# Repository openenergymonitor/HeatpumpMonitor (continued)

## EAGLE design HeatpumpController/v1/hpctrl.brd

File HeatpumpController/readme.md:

# Heatpump Controller v1

An initial board design for a heat pump controller, designed for use with a Mitsubishi EcoDan with a FTC2b controller.

This board sits on top of a RaspberryPi and the very basic at this stage python scripting that runs on it can be found here: https://github.com/TrystanLea/heatpump_control

**Features:**

- 6x solid state relay outputs either PVT312, PVT412 or LH1546. Most of these are used to switch the volts free inputs on the FTC2b, e.g heating on, DHW mode etc.
- The PVT412 can drive up to 120mA AC which is 27.6W, can directly control a couple of AC low power solenoids/valves.
- 4x DS18B20 temperature sensor connections for cylinder and outside temperature sensors
- 0-5V voltage output to set EcoDan flow temperature
- A connection for the MBUS reader module here [USB_to_MBUS](https://github.com/openenergymonitor/HeatpumpMonitor/tree/master/Hardware/USB_to_MBUS) to read from heat meters. Later version could integrate this on the board.
- The Pi can connect via an modbus reader to a SDM120 single phase electricity meter, see [OEM Guide](https://guide.openenergymonitor.org/integrations/emonhub-interfacers/#reading-from-a-sdm120-single-phase-meter)

## Alternative approach (better?)

It looks like it is possible to issue commands directly via the CN105 connector on most Mitsubushi EcoDan controllers, which looks like a better and much cheaper approach than the above. Will be trying this myself soon:

- https://github.com/SwiCago/HeatPump
- https://www.geekzone.co.nz/forums.asp?forumid=73&topicid=265469
- https://web.archive.org/web/20171007190023/https://nicegear.co.nz/blog/hacking-a-mitsubishi-heat-pump-air-conditioner/
- https://gitter.im/Mitsubishi-CN105-Protocol-Decode/community
- https://github.com/m000c400/Mitsubishi-CN105-Protocol-Decode
- https://github.com/BartGijsbers/CN105Gateway
- https://www.zakon.org/robert/projects/MiniSplitPi/

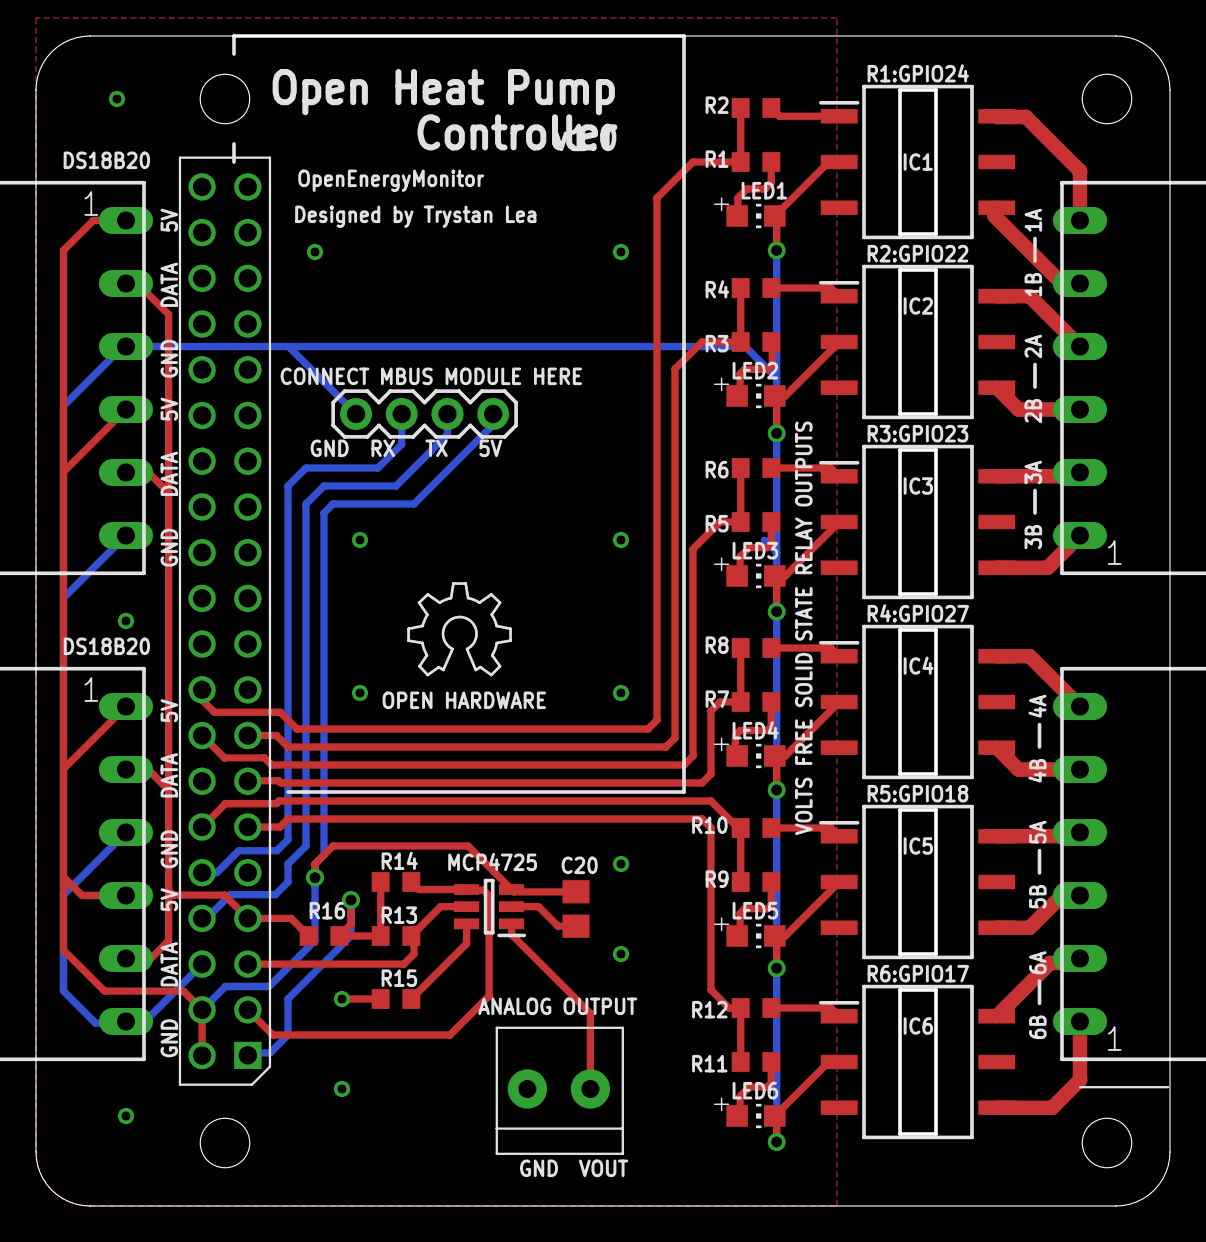
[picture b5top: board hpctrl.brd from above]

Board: 2 copper layers, 63.0 x 65.0 mm, 38 parts (0 on the bottom side), 40 nets.

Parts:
C20: 1uF; C0805
IC1, IC2, IC3, IC4, IC5, IC6: PVT312LSPBF; SOP254P978X342-6N
IC7: MCP4725A0T-E_CH; SOT95P270X145-6N
J1: 1X2-3.5MM
LED1, LED2, LED3, LED4, LED5, LED6: Red 1.85V; CHIP-LED0805
LOGO2: OSHW_LOGO_6MILX0200-NT; OSHW_6X200_NOTEXT
MBUS_SERIAL: 1X4-BIG; 1X04-BIG
PCB1: RPI3RPI3; RPI3
R1, R3, R4, R5, R6, R7, R8, R9, R10, R11, R12: 1K; R0603
R2: 1k; R0603
R13, R14, R15: 10k; R0603
R16: 4.7k; R0603
TB1, TB2, TB3, TB4: 3.5MM_TB_X6; 3.5MM_X6

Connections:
3V3: PCB1.P$1, R13.2, R14.2, R16.2
5V: C20.1, IC7.3, MBUS_SERIAL.1, PCB1.P$2, PCB1.P$4, TB3.P$1, TB3.P$4, TB4.P$1, TB4.P$4
DS18B20: PCB1.P$7, R16.1, TB3.P$2, TB3.P$5, TB4.P$2, TB4.P$5
GND: C20.2, IC1.2, IC2.2, IC3.2, IC4.2, IC5.2, IC6.2, IC7.2, J1.2, LED1.C, LED2.C, LED3.C, LED4.C, LED5.C, LED6.C, MBUS_SERIAL.4, PCB1.P$6, PCB1.P$9, R15.2, TB3.P$3, TB3.P$6, TB4.P$3, TB4.P$6
unnamed: IC1.1, R2.1
unnamed: IC7.1, J1.1
unnamed: LED2.A, R3.1
unnamed: IC2.1, R4.1
unnamed: LED3.A, R5.1
unnamed: IC3.1, R6.1
unnamed: LED4.A, R7.1
unnamed: IC4.1, R8.1
unnamed: LED5.A, R9.1
unnamed: IC5.1, R10.1
unnamed: LED6.A, R11.1
unnamed: IC6.1, R12.1
unnamed: IC7.6, R15.1
unnamed: LED1.A, R1.1
R1: PCB1.P$18, R1.2, R2.2
R1A: IC1.6, TB2.P$6
R1B: IC1.4, TB2.P$5
R2: PCB1.P$15, R3.2, R4.2
R2A: IC2.6, TB2.P$4
R2B: IC2.4, TB2.P$3
R3: PCB1.P$16, R5.2, R6.2
R3A: IC3.6, TB2.P$2
R3B: IC3.4, TB2.P$1
R4: PCB1.P$13, R7.2, R8.2
R4A: IC4.6, TB1.P$6
R4B: IC4.4, TB1.P$5
R5: PCB1.P$12, R9.2, R10.2
R5A: IC5.6, TB1.P$4
R5B: IC5.4, TB1.P$3
R6: PCB1.P$11, R11.2, R12.2
R6A: IC6.6, TB1.P$2
R6B: IC6.4, TB1.P$1
RXD: MBUS_SERIAL.3, PCB1.P$10
SCL: IC7.5, PCB1.P$5, R13.1
SDA: IC7.4, PCB1.P$3, R14.1
TXD: MBUS_SERIAL.2, PCB1.P$8

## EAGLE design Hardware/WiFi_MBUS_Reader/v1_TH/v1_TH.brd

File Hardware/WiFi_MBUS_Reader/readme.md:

# WiFi MBUS Reader

## Schematic

[WiFi_MBUS_Reader.brd](WiFi_MBUS_Reader.brd)

## Board

[WiFi_MBUS_Reader.sch](WiFi_MBUS_Reader.sch)

The hardware design (schematics, board files and gerber) files are licensed under the [Creative Commons Attribution-ShareAlike 3.0 Unported License](http://creativecommons.org/licenses/by-sa/3.0/) and follow the terms of the [OSHW (Open-source hardware) Statement of Principles 1.0.](http://freedomdefined.org/OSHW)

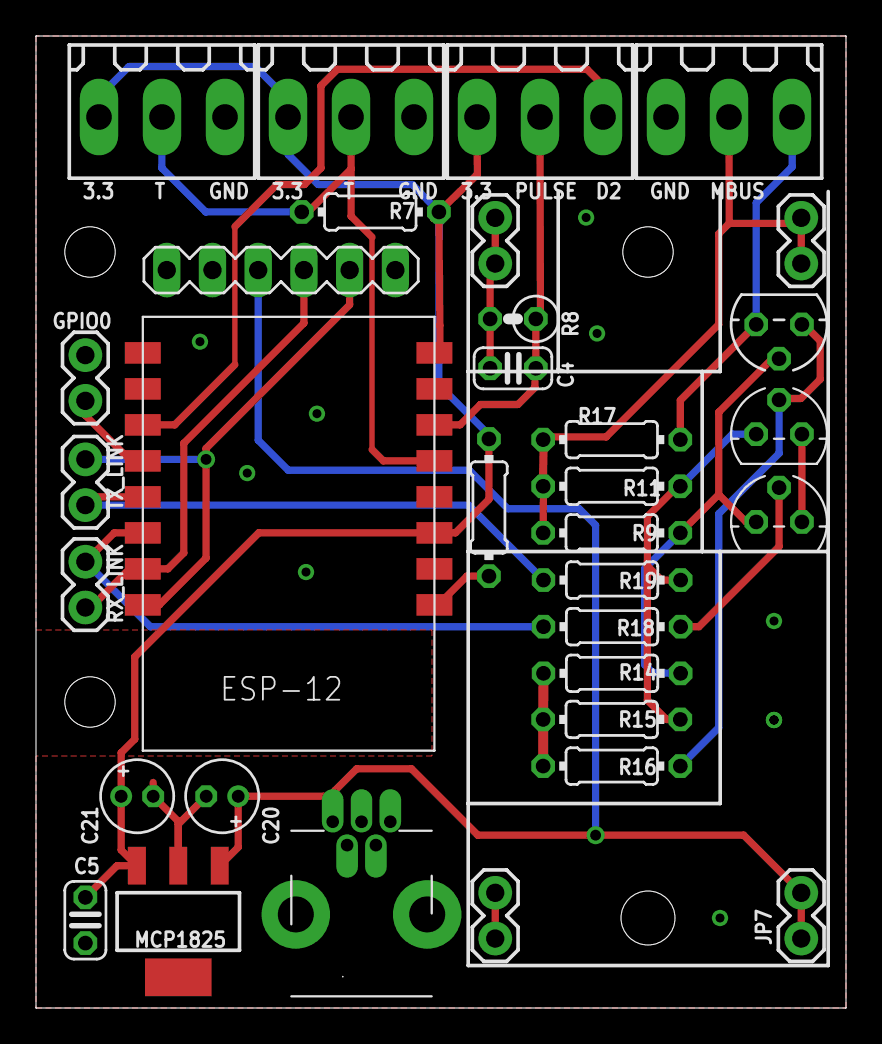
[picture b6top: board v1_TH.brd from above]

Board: 2 copper layers, 45.0 x 54.0 mm, 34 parts (1 on the bottom side), 18 nets.

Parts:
5VUSB: USB-MINIB-THM-MOLEX
C4, C5: 100nF; C025-024X044
C20, C21: 10µ; E1,8-4
FTDI1: FTDI; MA06-1
GPIO0: 1X02
JP4, JP5, JP6, JP7: 1X02
LOGO1: OSHW_LOGO_6MILX0200-NT; OSHW_6X200_NOTEXT
MCP1825: MCP1825SOT-223-3; SOT-223
Q1, Q2: BC337; TO92
R3: 10k; 0204/7
R7: 4.7K; 0204/7
R8: 100k; 0207/2V
R9: 39k; 0204/7
R11: 33k; 0204/7
R14: 22k; 0204/7
R15: 3k3; 0204/7
R16: 82r; 0204/7
R17: 220k; 0204/7
R18, R19: 1k; 0204/7
RX_LINK: 1X02
T1: BC307; TO92
T9: 180-3
TX_LINK: 1X02
U$1: ESP8266_ESP-12; ESP8266-ESP12
X1, X2, X7: 180-3

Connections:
3.3V: C5.2, C21.+, MCP1825.3, R3.2, R7.2, U$1.11, U$1.16, X1.3, X2.3, X7.3
5V: 5VUSB.VBUS, C20.+, FTDI1.4, JP7.1, JP7.2, MCP1825.1
24V: JP5.1, JP5.2, R9.2, R11.2, R17.2, T9.2
D12: R19.2, TX_LINK.2, U$1.5
D14: R18.2, RX_LINK.2, U$1.6
DS18B20: R7.1, U$1.13, X1.2, X2.2
ESPRX: FTDI1.3, RX_LINK.1, U$1.7
ESPTX: FTDI1.2, TX_LINK.1, U$1.8
GND: 5VUSB.GND, C4.1, C5.1, C20.-, C21.-, FTDI1.6, GPIO0.1, JP4.1, JP4.2, JP6.1, JP6.2, MCP1825.2, Q1.1, Q2.1, R8.2, R14.1, R15.1, R16.1, T9.3, U$1.1, U$1.2, X1.1, X2.1
GPIO2: U$1.3, X7.1
unnamed: R17.1, T1.1, T9.1
unnamed: Q2.2, R16.2, T1.3
unnamed: Q1.3, R9.1, R14.2, T1.2
unnamed: Q2.3, R11.1, R15.2, R19.1
unnamed: Q1.2, R18.1
unnamed: GPIO0.2, U$1.4
unnamed: R3.1, U$1.9
PULSE: C4.2, R8.1, U$1.14, X7.2

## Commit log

2016-02-10 Open source heatpump monitor arduino firmware, hardware and web dashboard
2016-02-10 images for readme
2016-02-22 Installation manual
2016-02-22 pulse input notes
2016-02-22 remove submodule
2016-02-22 Main firmware
2016-04-07 v2 of heatpump monitor PCB
2016-04-07 updated readme for v2
2016-05-26 Updated to include watchdog
2016-05-26 Improved debug output
2016-05-26 reset watchdog while scanning for mbus devices
2016-05-26 Option to read total wh from elster IRDA port
2016-05-26 Link to EmonESP and heatpump blog posts
2016-05-26 readme edits
2016-05-26 development outline
2016-05-26 Formatting
2016-06-05 Atmega firmware update
2016-06-05 change DS18B20 ordering
2016-06-07 More stable calculation of VFS flow and temperature
2016-06-22 Example one off prototype costing for heatpump monitor
2016-06-22 BOM + costing example html
2016-06-23 correction to PCB price
2016-06-24 Build notes
2016-06-24 resistor color codes
2016-06-24 Heatpump monitor and Energy Monitor build
2016-06-25 minor change
2016-06-25 move development to seperate page
2016-06-25 new development documentation page
2016-06-25 Costing examples
2016-06-26 v2 schematic and board image files
2016-06-26 BasicEnergyMonitor example
2016-06-26 updated connection diagram
2016-06-26 irda reader image
2016-06-26 kamstrup heat meter image
2016-06-26 flow meter images
2016-06-26 show as image
2016-06-26 CT energy monitor image
2016-06-26 EmonESP and emoncms inputs
2016-06-27 updated BOM image and costings
2016-06-30 v2 of fascia
2016-06-30 line thickness
2016-07-09 Tiled Fascia's for laser cutter
2016-07-09 fixed watt hour accumulator calc and addition of msg counter to heatpump monitor code
2016-07-09 missing comma
2016-07-11 removed heatpump dashboard replaced with emoncms energy, modification to name of Pulse/IRDA input
2016-07-12 software setup overview
2016-07-19 Selecting the right heat meter
2016-07-19 image path
2016-07-21 All arduino libraries needed for compilation
2016-07-26 option to disable CT sensing
2016-07-29 removed libraries
2016-07-29 Library files
2016-08-12 add support to compile with patformio
2016-08-12 readme lib
2016-08-12 remove temp files add git ignore
2016-08-17 add firmware upload link
2016-08-18 v3 of heatpump monitor design - voltage regulators
2016-08-28 Updated v3 board and shematic images
2016-09-08 updated picture
2016-09-08 latest image
2016-09-22 move msg print to after emon ct1 sample
2016-09-26 pubsublibrary required by EmonESP
2016-10-06 Moved the switched lables for R5 and R6 to their correct resistors on the BRD.
2016-10-21 Added tactile switch for reset button
2016-11-22 kamstrup mbus support for 403
2016-11-23 minor bug fixes for kamstrup 403 support
2016-11-24 Tidying up and track alignments
2016-11-24 gerbers for v4
2016-11-30 New firmware with automatic DS18B20 sensor address scanning
2016-12-12 fix missing new line
2016-12-12 - filter temperature below -50 and above 80 removing error modes -127 and 85 - option for CT only mode
2016-12-12 ct only mode
2017-02-14 use long instead of unsigned long for energy cumulative
2017-03-01 updated topgraphic
2017-03-01 updated sensors diagram
2017-03-01 updated images for heatpump monitor build
2017-03-01 updated heatpump monitor v4 image
2017-03-01 updated note on SMT voltage regulator
2017-03-01 updated BOM 1x
2017-03-01 updated software setup images
2017-03-01 apikey
2017-03-01 update installation guide
2017-03-01 update to include note about DS18B20 temperature sensors
2017-03-01 remcommended feed names
2017-03-02 v4 schematic and board file readme
2017-03-02 updated kit contents image
2017-03-02 mbus kit bom
2017-03-02 updated BOM and costing
2017-03-02 updated costing
2017-03-02 updating 1x costing table example
2017-03-02 update costing
2017-03-02 build guide pictures
2017-03-02 enclosure images
2017-06-13 Heatpump Monitor sketch to run on EmonTx v3 to use with WIFI module
2017-06-22 changes to variable names
2017-07-29 Correction: data is not sent via RFM69
    Correction: data is not sent via RFM69
2017-08-19 CT3 Solder Jumper
2017-12-07 updated firmware to support sontex heat meter
2017-12-11 fix ds18b20 temp bug
2017-12-11 reorder ds18b20 temperature sensor read
2017-12-11 cut down example for sontex meter
2017-12-12 set correct delays enable OEM CT monitoring as default
2017-12-12 Update to libraries (latest compilation)
2017-12-12 Script for fetching latest libraries
2017-12-12 onewire library reference
2017-12-12 compiled version of latest firmware
2017-12-12 fix vfs measurement
2017-12-12 memory use improvements + refactor
2017-12-13 remove sontex firmware
2017-12-13 sontex note
2017-12-17 MBUS Reader tool
2017-12-17 improved mbus implementation & sontex 531 support
2017-12-17 change default baud rate to 2400 and allow for maximum frame
2017-12-17 change defaults
2018-01-23 multipage sontex data read support
2018-02-03 Additional VIF decoding
    These are the additional VIFs that my meter provides, as well as differentiating between values that are instantaneous and those that are averaged.
2018-05-30 compiled hex file and upload command
2018-05-30 check for ack and delay 500ms
2019-01-10 fix sontex 531 support
2019-01-16 control firmware
2019-01-31 remove multipage control, moved to esp module
2019-10-07 fix dashboard documentation
2020-09-03 new design: WiFi MBUS Reader
2020-11-25 new MBUS reader hardware designs
2020-11-25 readme update
2020-11-25 picture of through-hole board and basic reader firmware for ESP8266
2020-11-25 usb to mbus readme
2021-01-26 v1 of heatpump controller board
2021-07-16 heat pump monitor Pi base board and latest USB to MBUS reader
2021-08-15 Organise by hardware designs
2021-08-15 images
2021-08-29 update images
2021-08-29 connection diagram
2021-09-02 display image
2021-09-13 updated pressure loss chart
2021-09-13 pressure loss spread sheet
2021-09-13 heat meter images
2021-09-13 update main readme
2021-10-11 Expand on technical details of Sontex meters
